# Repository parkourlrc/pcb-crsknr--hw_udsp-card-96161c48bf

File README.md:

# uDSP-Card: XCORE.AI Development Board for Portable Applications

This repository contains the hardware design files, pinout, and architectural documentation for the uDSP-Card, a small development board built around the XMOS XU316. Originally designed for a wearable ultrasonic sensing system, the board offers rich I/O and high-performance DSP capabilities at low power, making it ideal for audio, sensing, and real-time embedded tasks.

This repository accompanies the blog post "[uDSP-Card: XCORE.AI Development Board for Portable Applications](https://crsknr.github.io/blog/blog/udsp-card)".

## Repository Contents

- `kicad_udsp-card/`: KiCAD project folder containing schematics and PCB layout  
- `uDSP-Card_HAD.pdf`: Hardware architecture design (HAD) documentation  
- `uDSP-Card_XMOS-XU316-pinout.xlsx`: Processor pin assignments

## Board Overview

The uDSP-Card is powered by the XMOS XU316, a dual-core, 800 MHz processor with 16 logical cores and a vector unit. The board is derived from the XMOS reference design and development board XK-EVK-XU316[^1].

### Key Specifications

- **Dimensions:** 60 mm × 30 mm (6-layer PCB)
- **Processor:** XMOS XU316-1024 (dual-core, 800 MHz, 16 threads)
- **RAM:** 128 Mb LPDDR1
- **Flash:** 32 Mb QSPI
- **microSD** card slot
- **USB Interface:** Device (power + audio/data)
- **Line Output:** Stereo via ESS ES9033 DAC
- **Expansion Header:** 44-pin interconnect
  - I²S (8ch)
  - I²C / SPI
  - PDM (8ch)
  - Power input
- **Onboard Sensors:**
  - BMI323 IMU (accelerometer + gyro)
  - BME280 EMU (humidity, pressure, temperature)

## Board support

[`lib_udsp-card_board_support`](https://github.com/crsknr/lib_udsp-card_board_support): XMOS board support package and configuration files for firmware development.

## License

This project is licensed under the [GNU General Public License v3.0](https://www.gnu.org/licenses/gpl-3.0.en.html).

[^1]: **XMOS**, *"xcore.ai Explorer v2 BoardManual"*, Manual XM014531A, (2024)

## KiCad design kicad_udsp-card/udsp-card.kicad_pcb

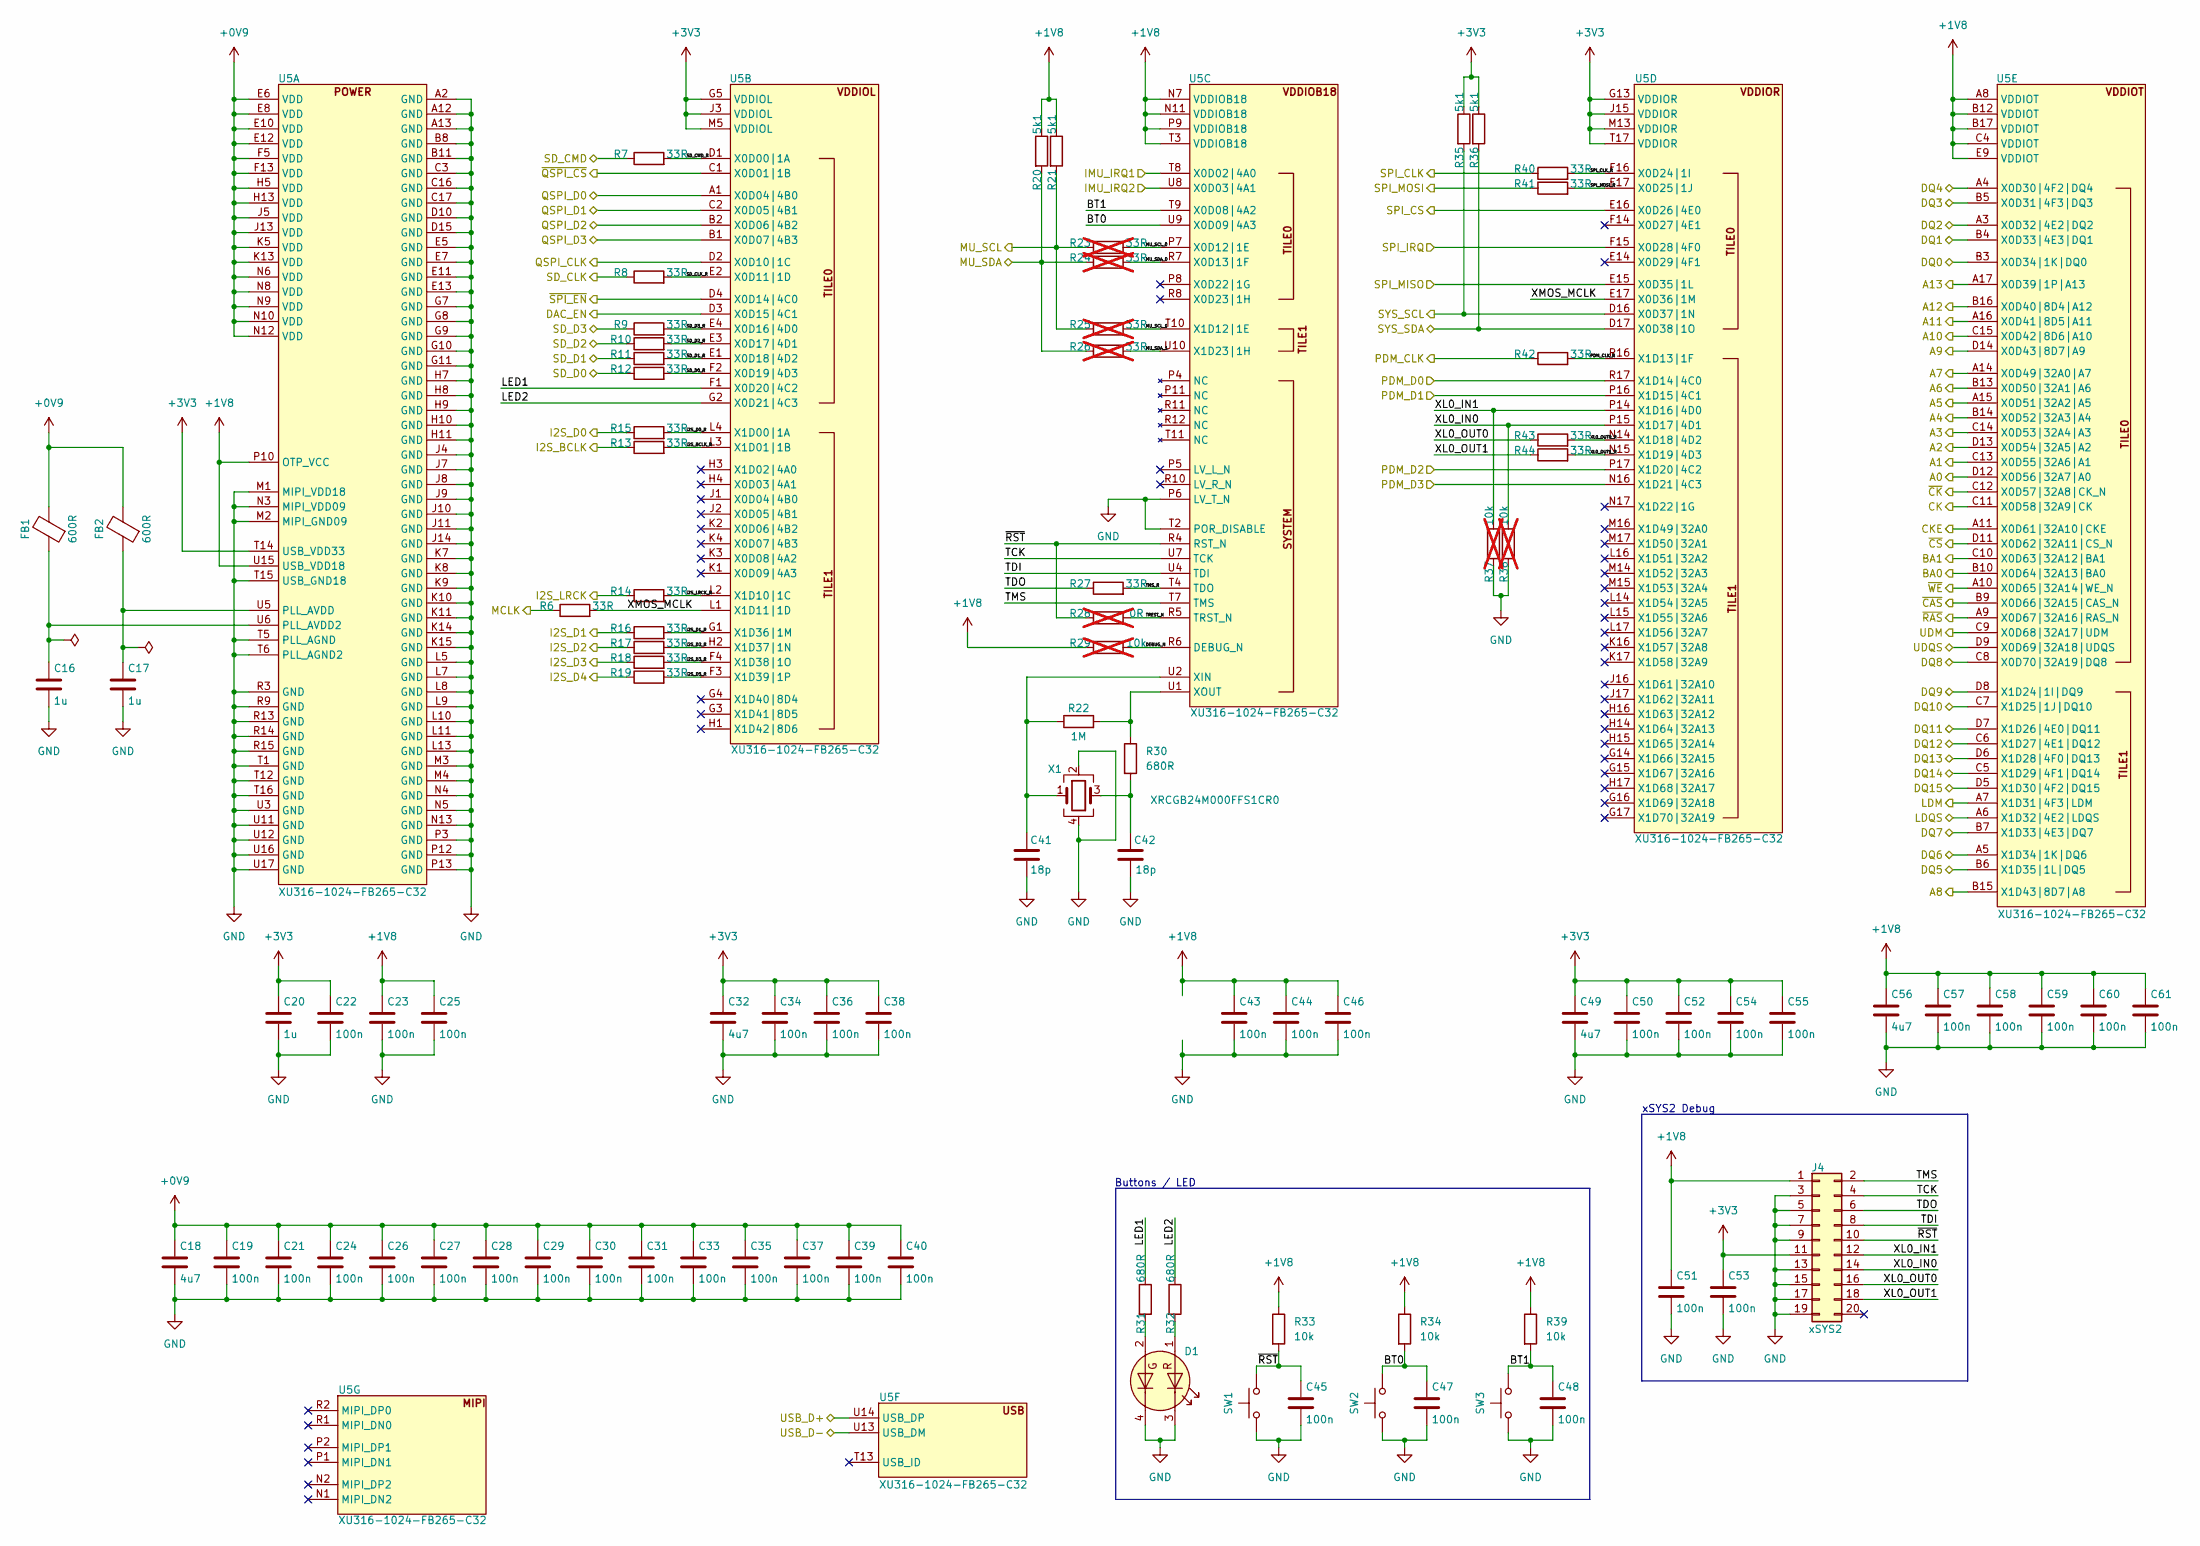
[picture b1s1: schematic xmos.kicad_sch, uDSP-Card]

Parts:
C16, C17, C20: 1u; C_0402_1005Metric; Part Number CC0402KRX5R7BB105
C18, C32, C49, C56: 4u7; C_0603_1608Metric; Part Number CC0603KRX5R7BB475
C19, C21, C22, C23, C24, C25, C26, C27, C28, C29, C30, C31, C33, C34, C35, C36, C37, C38, C39, C40, C43, C44, C45, C46, C47, C48, C50, C51, C52, C53, C54, C55, C57, C58, C59, C60, C61: 100n; C_0402_1005Metric; Part Number CC0402KRX5R9BB104
C41, C42: 18p; C_0402_1005Metric; Part Number CC0402JRNPO9BN180
D1: LTST-C195KGJRKT; LTST-C195KGJRKT-NPC_LTO; Part Number LTST-C195KGJRKT
FB1, FB2: 600R; L_0402_1005Metric; Part Number BLM15PX601SH1D
J4: xSYS2; SAMTEC_FTSH-110-01-F-DV-TR; Part Number FTSH-110-01-F-DV-K
R6, R7, R8, R9, R10, R11, R12, R13, R14, R15, R16, R17, R18, R19, R27, R40, R41, R42, R43, R44: 33R; R_0402_1005Metric; Part Number RC0402FR-0733RL
R20, R21, R35, R36: 5k1; R_0402_1005Metric; Part Number RC0402FR-075K1L
R22: 1M; R_0402_1005Metric; Part Number RC0402FR-071ML
R23, R24, R25, R26: 33R; R_0402_1005Metric; Part Number RC0402FR-7D33RL; not fitted
R28: 0R; R_0402_1005Metric; not fitted
R29, R37, R38: 10k; R_0402_1005Metric; not fitted
R30, R31, R32: 680R; R_0402_1005Metric; Part Number RC0402FR-07680RL
R33, R34, R39: 10k; R_0402_1005Metric; Part Number RC0402FR-0710KL
SW1, SW2, SW3: EVQ-P2F02K; EVQP2K_PAN; Part Number EVQ-P2F02K
U5: XU316-1024-FB265-C32; TFBGA-265_14x14mm_Layout17x17_P0.8mm; Part Number XU316-1024-FB265-C32
X1: XRCGB24M000FFS1CR0; XRCGB24_MUR; Part Number XRCGB24M000FFS1CR0

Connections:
+0V9: C18.1, C19.1, C21.1, C24.1, C26.1, C27.1, C28.1, C29.1, C30.1, C31.1, C33.1, C35.1, C37.1, C39.1, C40.1, FB1.2, FB2.2, U5.E6 (VDD), U5.E8 (VDD), U5.E10 (VDD), U5.E12 (VDD), U5.F5 (VDD), U5.F13 (VDD), U5.H5 (VDD), U5.H13 (VDD), U5.J5 (VDD), U5.J13 (VDD), U5.K5 (VDD), U5.K13 (VDD), U5.N6 (VDD), U5.N8 (VDD), U5.N9 (VDD), U5.N10 (VDD), U5.N12 (VDD); also elsewhere on the board
+1V8: C23.1, C25.1, C43.1, C44.1, C46.1, C51.1, C56.1, C57.1, C58.1, C59.1, C60.1, C61.1, J4.1, R20.1, R21.1, R29.1, R33.1, R34.1, R39.1, U5.A8 (VDDIOT), U5.B12 (VDDIOT), U5.B17 (VDDIOT), U5.C4 (VDDIOT), U5.E9 (VDDIOT), U5.N7 (VDDIOB18), U5.N11 (VDDIOB18), U5.P9 (VDDIOB18), U5.P10 (OTP_VCC), U5.T3 (VDDIOB18), U5.U15 (USB_VDD18); also elsewhere on the board
+3V3: C20.1, C22.1, C32.1, C34.1, C36.1, C38.1, C49.1, C50.1, C52.1, C53.1, C54.1, C55.1, J4.11, R35.1, R36.1, U5.G5 (VDDIOL), U5.G13 (VDDIOR), U5.J3 (VDDIOL), U5.J15 (VDDIOR), U5.M5 (VDDIOL), U5.M13 (VDDIOR), U5.T14 (USB_VDD33), U5.T17 (VDDIOR); also elsewhere on the board
/DAC_EN: U5.D3 (X0D15|4C1); also elsewhere on the board
/I2S.BCLK: R13.1; also elsewhere on the board
/I2S.D0: R15.1; also elsewhere on the board
/I2S.D1: R16.1; also elsewhere on the board
/I2S.D2: R17.1; also elsewhere on the board
/I2S.D3: R18.1; also elsewhere on the board
/I2S.D4: R19.1; also elsewhere on the board
/I2S.LRCK: R14.1; also elsewhere on the board
/I2S.MCLK: R6.1; also elsewhere on the board
/IMU_IRQ1: U5.T8 (X0D02|4A0); also elsewhere on the board
/IMU_IRQ2: U5.U8 (X0D03|4A1); also elsewhere on the board
/LPDDR_ADDR.A0: U5.D12 (X0D56|32A7|A0); also elsewhere on the board
/LPDDR_ADDR.A1: U5.C13 (X0D55|32A6|A1); also elsewhere on the board
/LPDDR_ADDR.A2: U5.D13 (X0D54|32A5|A2); also elsewhere on the board
/LPDDR_ADDR.A3: U5.C14 (X0D53|32A4|A3); also elsewhere on the board
/LPDDR_ADDR.A4: U5.B14 (X0D52|32A3|A4); also elsewhere on the board
/LPDDR_ADDR.A5: U5.A15 (X0D51|32A2|A5); also elsewhere on the board
/LPDDR_ADDR.A6: U5.B13 (X0D50|32A1|A6); also elsewhere on the board
/LPDDR_ADDR.A7: U5.A14 (X0D49|32A0|A7); also elsewhere on the board
/LPDDR_ADDR.A8: U5.B15 (X1D43|8D7|A8); also elsewhere on the board
/LPDDR_ADDR.A9: U5.D14 (X0D43|8D7|A9); also elsewhere on the board
/LPDDR_ADDR.A10: U5.C15 (X0D42|8D6|A10); also elsewhere on the board
/LPDDR_ADDR.A11: U5.A16 (X0D41|8D5|A11); also elsewhere on the board
/LPDDR_ADDR.A12: U5.B16 (X0D40|8D4|A12); also elsewhere on the board
/LPDDR_ADDR.A13: U5.A17 (X0D39|1P|A13); also elsewhere on the board
/LPDDR_CTRL.BA0: U5.B10 (X0D64|32A13|BA0); also elsewhere on the board
/LPDDR_CTRL.BA1: U5.C10 (X0D63|32A12|BA1); also elsewhere on the board
/LPDDR_CTRL.CK+: U5.C11 (X0D58|32A9|CK); also elsewhere on the board
/LPDDR_CTRL.CK-: U5.C12 (X0D57|32A8|CK_N); also elsewhere on the board
/LPDDR_CTRL.CKE: U5.A11 (X0D61|32A10|CKE); also elsewhere on the board
/LPDDR_CTRL.~CAS: U5.B9 (X0D66|32A15|CAS_N); also elsewhere on the board
/LPDDR_CTRL.~CS: U5.D11 (X0D62|32A11|CS_N); also elsewhere on the board
/LPDDR_CTRL.~RAS: U5.A9 (X0D67|32A16|RAS_N); also elsewhere on the board
/LPDDR_CTRL.~WE: U5.A10 (X0D65|32A14|WE_N); also elsewhere on the board
/LPDDR_LD.DQ0: U5.B3 (X0D34|1K|DQ0); also elsewhere on the board
/LPDDR_LD.DQ1: U5.B4 (X0D33|4E3|DQ1); also elsewhere on the board
/LPDDR_LD.DQ2: U5.A3 (X0D32|4E2|DQ2); also elsewhere on the board
/LPDDR_LD.DQ3: U5.B5 (X0D31|4F3|DQ3); also elsewhere on the board
/LPDDR_LD.DQ4: U5.A4 (X0D30|4F2|DQ4); also elsewhere on the board
/LPDDR_LD.DQ5: U5.B6 (X1D35|1L|DQ5); also elsewhere on the board
/LPDDR_LD.DQ6: U5.A5 (X1D34|1K|DQ6); also elsewhere on the board
/LPDDR_LD.DQ7: U5.B7 (X1D33|4E3|DQ7); also elsewhere on the board
/LPDDR_LD.LDM: U5.A7 (X1D31|4F3|LDM); also elsewhere on the board
/LPDDR_LD.LDQS: U5.A6 (X1D32|4E2|LDQS); also elsewhere on the board
/LPDDR_UD.DQ8: U5.C8 (X0D70|32A19|DQ8); also elsewhere on the board
/LPDDR_UD.DQ9: U5.D8 (X1D24|1I|DQ9); also elsewhere on the board
/LPDDR_UD.DQ10: U5.C7 (X1D25|1J|DQ10); also elsewhere on the board
/LPDDR_UD.DQ11: U5.D7 (X1D26|4E0|DQ11); also elsewhere on the board
/LPDDR_UD.DQ12: U5.C6 (X1D27|4E1|DQ12); also elsewhere on the board
/LPDDR_UD.DQ13: U5.D6 (X1D28|4F0|DQ13); also elsewhere on the board
/LPDDR_UD.DQ14: U5.C5 (X1D29|4F1|DQ14); also elsewhere on the board
/LPDDR_UD.DQ15: U5.D5 (X1D30|4F2|DQ15); also elsewhere on the board
/LPDDR_UD.UDM: U5.C9 (X0D68|32A17|UDM); also elsewhere on the board
/LPDDR_UD.UDQS: U5.D9 (X0D69|32A18|UDQS); also elsewhere on the board
/MIC.CLK: R42.1; also elsewhere on the board
/MIC.D0: U5.R17 (X1D14|4C0); also elsewhere on the board
/MIC.D1: U5.P16 (X1D15|4C1); also elsewhere on the board
/MIC.D2: U5.P17 (X1D20|4C2); also elsewhere on the board
/MIC.D3: U5.N16 (X1D21|4C3); also elsewhere on the board
/MU.SCL: R21.2, R23.1, R25.1; also elsewhere on the board
/MU.SDA: R20.2, R24.1, R26.1; also elsewhere on the board
/QSPI.CLK: U5.D2 (X0D10|1C); also elsewhere on the board
/QSPI.D0: U5.A1 (X0D04|4B0); also elsewhere on the board
/QSPI.D1: U5.C2 (X0D05|4B1); also elsewhere on the board
/QSPI.D2: U5.B2 (X0D06|4B2); also elsewhere on the board
/QSPI.D3: U5.B1 (X0D07|4B3); also elsewhere on the board
/QSPI.~CS: U5.C1 (X0D01|1B); also elsewhere on the board
/SD.CLK: R8.1; also elsewhere on the board
/SD.CMD: R7.1; also elsewhere on the board
/SD.D0: R12.1; also elsewhere on the board
/SD.D1: R11.1; also elsewhere on the board
/SD.D2: R10.1; also elsewhere on the board
/SD.D3: R9.1; also elsewhere on the board
/SPI.CLK: R40.1; also elsewhere on the board
/SPI.CS: U5.E16 (X0D26|4E0); also elsewhere on the board
/SPI.MISO: U5.E15 (X0D35|1L); also elsewhere on the board
/SPI.MOSI: R41.1; also elsewhere on the board
/SPI_IRQ: U5.F15 (X0D28|4F0); also elsewhere on the board
/SYS.SCL: R35.2, U5.D16 (X0D37|1N); also elsewhere on the board
/SYS.SDA: R36.2, U5.D17 (X0D38|1O); also elsewhere on the board
/USB.D+: U5.U14 (USB_DP); also elsewhere on the board
/USB.D-: U5.U13 (USB_DM); also elsewhere on the board
/XMOS/BT0: C47.1, R34.2, SW2.2, U5.U9 (X0D09|4A3)
/XMOS/BT1: C48.1, R39.2, SW3.2, U5.T9 (X0D08|4A2)
/XMOS/DEBUG_N: R29.2, U5.R6 (DEBUG_N)
/XMOS/I2S_BCLK_R: R13.2, U5.L3 (X1D01|1B)
/XMOS/I2S_D0_R: R15.2, U5.L4 (X1D00|1A)
/XMOS/I2S_D1_R: R16.2, U5.G1 (X1D36|1M)
/XMOS/I2S_D2_R: R17.2, U5.H2 (X1D37|1N)
/XMOS/I2S_D3_R: R18.2, U5.F4 (X1D38|1O)
/XMOS/I2S_D5_R: R19.2, U5.F3 (X1D39|1P)
/XMOS/I2S_LRCK_R: R14.2, U5.L2 (X1D10|1C)
/XMOS/LED1: R31.1, U5.F1 (X0D20|4C2)
/XMOS/LED2: R32.1, U5.G2 (X0D21|4C3)
/XMOS/MU_SCL_0: R23.2, U5.P7 (X0D12|1E)
/XMOS/MU_SCL_1: R25.2, U5.T10 (X1D12|1E)
/XMOS/MU_SDA_0: R24.2, U5.R7 (X0D13|1F)
/XMOS/MU_SDA_1: R26.2, U5.U10 (X1D23|1H)
/XMOS/PDM_CLK_R: R42.2, U5.R16 (X1D13|1F)
/XMOS/SD_CLK_R: R8.2, U5.E2 (X0D11|1D)
/XMOS/SD_CMD_R: R7.2, U5.D1 (X0D00|1A)
/XMOS/SD_D0_R: R12.2, U5.F2 (X0D19|4D3)
/XMOS/SD_D1_R: R11.2, U5.E1 (X0D18|4D2)
/XMOS/SD_D2_R: R10.2, U5.E3 (X0D17|4D1)
/XMOS/SD_D3_R: R9.2, U5.E4 (X0D16|4D0)
/XMOS/SPI_CLK_R: R40.2, U5.F16 (X0D24|1I)
/XMOS/SPI_MOSI_R: R41.2, U5.F17 (X0D25|1J)
/XMOS/TCK: J4.4, U5.U7 (TCK)
/XMOS/TDI: J4.8, U5.U4 (TDI)
/XMOS/TDO: J4.6, R27.1
/XMOS/TMS: J4.2, U5.T7 (TMS)
/XMOS/TMS_R: R27.2, U5.T4 (TDO)
/XMOS/TREST_N: R28.2, U5.R5 (TRST_N)
/XMOS/XL0_IN0: J4.14, R38.2, U5.P15 (X1D17|4D1)
/XMOS/XL0_IN1: J4.12, R37.2, U5.P14 (X1D16|4D0)
/XMOS/XL0_OUT0: J4.16, R43.1
/XMOS/XL0_OUT0_R: R43.2, U5.N14 (X1D18|4D2)
/XMOS/XL0_OUT1: J4.18, R44.1
/XMOS/XL0_OUT1_R: R44.2, U5.N15 (X1D19|4D3)
/XMOS/XMOS_MCLK: R6.2, U5.E17 (X0D36|1M), U5.L1 (X1D11|1D)
/XMOS/~RST: C45.1, J4.10, R28.1, R33.2, SW1.2, U5.R4 (RST_N)
/~SPI_EN: U5.D4 (X0D14|4C0); also elsewhere on the board
GND: C16.2, C17.2, C18.2, C19.2, C20.2, C21.2, C22.2, C23.2, C24.2, C25.2, C26.2, C27.2, C28.2, C29.2, C30.2, C31.2, C32.2, C33.2, C34.2, C35.2, C36.2, C37.2, C38.2, C39.2, C40.2, C41.2, C42.2, C43.2, C44.2, C45.2, C46.2, C47.2, C48.2, C49.2, C50.2, C51.2, C52.2, C53.2, C54.2, C55.2, C56.2, C57.2, C58.2, C59.2, C60.2, C61.2, D1.3 (K1), D1.4 (K2), J4.3, J4.5, J4.7, J4.9, J4.13, J4.15, J4.17, J4.19, R37.1, R38.1, SW1.1, SW2.1, SW3.1, U5.A2 (GND), U5.A12 (GND), U5.A13 (GND), U5.B8 (GND), U5.B11 (GND), U5.C3 (GND), U5.C16 (GND), U5.C17 (GND), U5.D10 (GND), U5.D15 (GND), U5.E5 (GND), U5.E7 (GND), U5.E11 (GND), U5.E13 (GND), U5.G7 (GND), U5.G8 (GND), U5.G9 (GND), U5.G10 (GND), U5.G11 (GND), U5.H7 (GND), U5.H8 (GND), U5.H9 (GND), U5.H10 (GND), U5.H11 (GND), U5.J4 (GND), U5.J7 (GND), U5.J8 (GND), U5.J9 (GND), U5.J10 (GND), U5.J11 (GND), U5.J14 (GND), U5.K7 (GND), U5.K8 (GND), U5.K9 (GND), U5.K10 (GND), U5.K11 (GND), U5.K14 (GND), U5.K15 (GND), U5.L5 (GND), U5.L7 (GND), U5.L8 (GND), U5.L9 (GND), U5.L10 (GND), U5.L11 (GND), U5.L13 (GND), U5.M1 (MIPI_VDD18), U5.M2 (MIPI_GND09), U5.M3 (GND), U5.M4 (GND), U5.N3 (MIPI_VDD09), U5.N4 (GND), U5.N5 (GND), U5.N13 (GND), U5.P3 (GND), U5.P6 (LV_T_N), U5.P12 (GND), U5.P13 (GND), U5.R3 (GND), U5.R9 (GND), U5.R13 (GND), U5.R14 (GND), U5.R15 (GND), U5.T1 (GND), U5.T2 (POR_DISABLE), U5.T5 (PLL_AGND), U5.T6 (PLL_AGND2), U5.T12 (GND), U5.T15 (USB_GND18), U5.T16 (GND), U5.U3 (GND), U5.U11 (GND), U5.U12 (GND), U5.U16 (GND), U5.U17 (GND), X1.2, X1.4; also elsewhere on the board
unnamed: C42.1, R30.2, X1.3
unnamed: D1.1 (A1), R32.2
unnamed: D1.2 (A2), R31.2
unnamed: C16.1, FB1.1, U5.U6 (PLL_AVDD2)
unnamed: C17.1, FB2.1, U5.U5 (PLL_AVDD)
unnamed: C41.1, R22.1, U5.U2 (XIN), X1.1
unnamed: R22.2, R30.1, U5.U1 (XOUT)

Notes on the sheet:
Buttons / LED
xSYS2 Debug

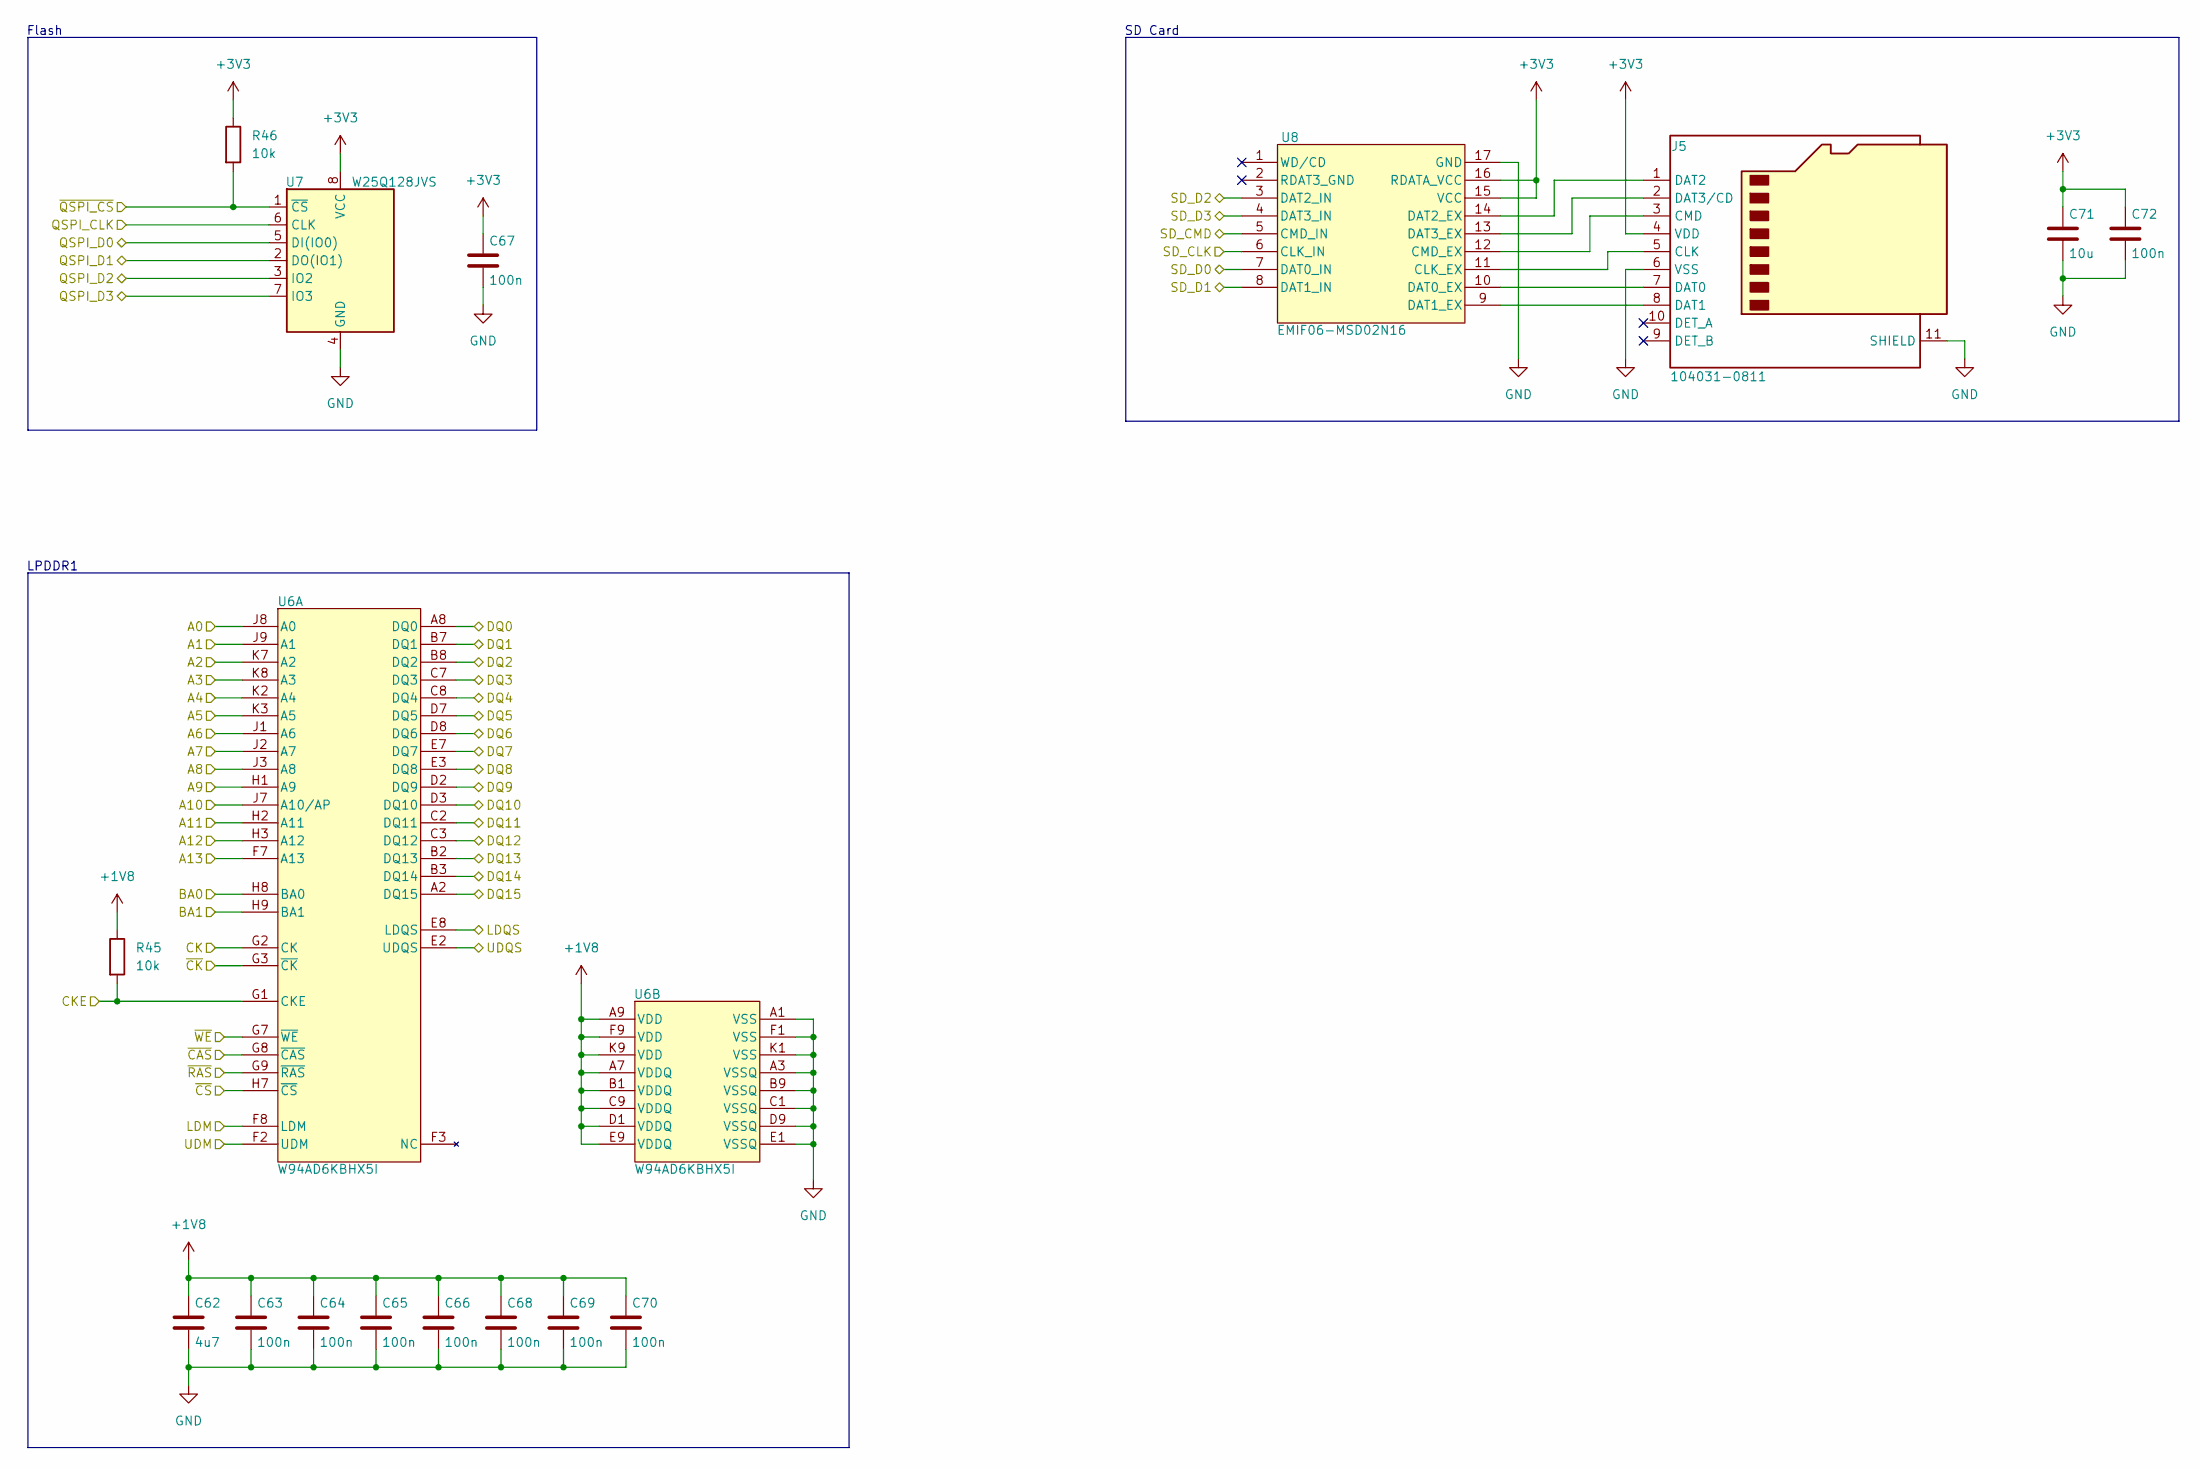
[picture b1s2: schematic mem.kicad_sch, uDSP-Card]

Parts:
C62: 4u7; C_0603_1608Metric; Part Number CC0603KRX5R7BB475
C63, C64, C65, C66, C67, C68, C69, C70, C72: 100n; C_0402_1005Metric; Part Number CC0402KRX5R9BB104
C71: 10u; C_0603_1608Metric; Part Number CC0603MRX5R7BB106
J5: 104031-0811; microSD_HC_Molex_104031-0811; Part Number 104031-0811
R45, R46: 10k; R_0402_1005Metric; Part Number RC0402FR-0710KL
U6: W94AD6KBHX5I; WIN_VFBGA-60_WIN; Part Number W94AD6KBHX5I
U7: W25Q128JVS; SOIC-8_5.23x5.23mm_P1.27mm; Part Number W25Q128JVSIM
U8: EMIF06-MSD02N16; MICROQFN16_1P25X3P55X0P4_STM; Part Number EMIF06-MSD02N16

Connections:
+1V8: C62.1, C63.1, C64.1, C65.1, C66.1, C68.1, C69.1, C70.1, R45.1, U6.A7 (VDDQ), U6.A9 (VDD), U6.B1 (VDDQ), U6.C9 (VDDQ), U6.D1 (VDDQ), U6.E9 (VDDQ), U6.F9 (VDD), U6.K9 (VDD); also elsewhere on the board
+3V3: C67.1, C71.1, C72.1, J5.4 (VDD), R46.1, U7.8 (VCC), U8.15 (VCC), U8.16 (RDATA_VCC); also elsewhere on the board
/LPDDR_ADDR.A0: U6.J8 (A0); also elsewhere on the board
/LPDDR_ADDR.A1: U6.J9 (A1); also elsewhere on the board
/LPDDR_ADDR.A2: U6.K7 (A2); also elsewhere on the board
/LPDDR_ADDR.A3: U6.K8 (A3); also elsewhere on the board
/LPDDR_ADDR.A4: U6.K2 (A4); also elsewhere on the board
/LPDDR_ADDR.A5: U6.K3 (A5); also elsewhere on the board
/LPDDR_ADDR.A6: U6.J1 (A6); also elsewhere on the board
/LPDDR_ADDR.A7: U6.J2 (A7); also elsewhere on the board
/LPDDR_ADDR.A8: U6.J3 (A8); also elsewhere on the board
/LPDDR_ADDR.A9: U6.H1 (A9); also elsewhere on the board
/LPDDR_ADDR.A10: U6.J7 (A10/AP); also elsewhere on the board
/LPDDR_ADDR.A11: U6.H2 (A11); also elsewhere on the board
/LPDDR_ADDR.A12: U6.H3 (A12); also elsewhere on the board
/LPDDR_ADDR.A13: U6.F7 (A13); also elsewhere on the board
/LPDDR_CTRL.BA0: U6.H8 (BA0); also elsewhere on the board
/LPDDR_CTRL.BA1: U6.H9 (BA1); also elsewhere on the board
/LPDDR_CTRL.CK+: U6.G2 (CK); also elsewhere on the board
/LPDDR_CTRL.CK-: U6.G3 (~CK); also elsewhere on the board
/LPDDR_CTRL.CKE: R45.2, U6.G1 (CKE); also elsewhere on the board
/LPDDR_CTRL.~CAS: U6.G8 (~CAS); also elsewhere on the board
/LPDDR_CTRL.~CS: U6.H7 (~CS); also elsewhere on the board
/LPDDR_CTRL.~RAS: U6.G9 (~RAS); also elsewhere on the board
/LPDDR_CTRL.~WE: U6.G7 (~WE); also elsewhere on the board
/LPDDR_LD.DQ0: U6.A8 (DQ0); also elsewhere on the board
/LPDDR_LD.DQ1: U6.B7 (DQ1); also elsewhere on the board
/LPDDR_LD.DQ2: U6.B8 (DQ2); also elsewhere on the board
/LPDDR_LD.DQ3: U6.C7 (DQ3); also elsewhere on the board
/LPDDR_LD.DQ4: U6.C8 (DQ4); also elsewhere on the board
/LPDDR_LD.DQ5: U6.D7 (DQ5); also elsewhere on the board
/LPDDR_LD.DQ6: U6.D8 (DQ6); also elsewhere on the board
/LPDDR_LD.DQ7: U6.E7 (DQ7); also elsewhere on the board
/LPDDR_LD.LDM: U6.F8 (LDM); also elsewhere on the board
/LPDDR_LD.LDQS: U6.E8 (LDQS); also elsewhere on the board
/LPDDR_UD.DQ8: U6.E3 (DQ8); also elsewhere on the board
/LPDDR_UD.DQ9: U6.D2 (DQ9); also elsewhere on the board
/LPDDR_UD.DQ10: U6.D3 (DQ10); also elsewhere on the board
/LPDDR_UD.DQ11: U6.C2 (DQ11); also elsewhere on the board
/LPDDR_UD.DQ12: U6.C3 (DQ12); also elsewhere on the board
/LPDDR_UD.DQ13: U6.B2 (DQ13); also elsewhere on the board
/LPDDR_UD.DQ14: U6.B3 (DQ14); also elsewhere on the board
/LPDDR_UD.DQ15: U6.A2 (DQ15); also elsewhere on the board
/LPDDR_UD.UDM: U6.F2 (UDM); also elsewhere on the board
/LPDDR_UD.UDQS: U6.E2 (UDQS); also elsewhere on the board
/QSPI.CLK: U7.6 (CLK); also elsewhere on the board
/QSPI.D0: U7.5 (DI(IO0)); also elsewhere on the board
/QSPI.D1: U7.2 (DO(IO1)); also elsewhere on the board
/QSPI.D2: U7.3 (IO2); also elsewhere on the board
/QSPI.D3: U7.7 (IO3); also elsewhere on the board
/QSPI.~CS: R46.2, U7.1 (~CS); also elsewhere on the board
/SD.CLK: U8.6 (CLK_IN); also elsewhere on the board
/SD.CMD: U8.5 (CMD_IN); also elsewhere on the board
/SD.D0: U8.7 (DAT0_IN); also elsewhere on the board
/SD.D1: U8.8 (DAT1_IN); also elsewhere on the board
/SD.D2: U8.3 (DAT2_IN); also elsewhere on the board
/SD.D3: U8.4 (DAT3_IN); also elsewhere on the board
GND: C62.2, C63.2, C64.2, C65.2, C66.2, C67.2, C68.2, C69.2, C70.2, C71.2, C72.2, J5.6 (VSS), J5.11 (SHIELD), U6.A1 (VSS), U6.A3 (VSSQ), U6.B9 (VSSQ), U6.C1 (VSSQ), U6.D9 (VSSQ), U6.E1 (VSSQ), U6.F1 (VSS), U6.K1 (VSS), U7.4 (GND), U8.17 (GND); also elsewhere on the board
unnamed: J5.5 (CLK), U8.11 (CLK_EX)
unnamed: J5.3 (CMD), U8.12 (CMD_EX)
unnamed: J5.7 (DAT0), U8.10 (DAT0_EX)
unnamed: J5.8 (DAT1), U8.9 (DAT1_EX)
unnamed: J5.1 (DAT2), U8.14 (DAT2_EX)
unnamed: J5.2 (DAT3/CD), U8.13 (DAT3_EX)

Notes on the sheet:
SD Card
Flash
LPDDR1

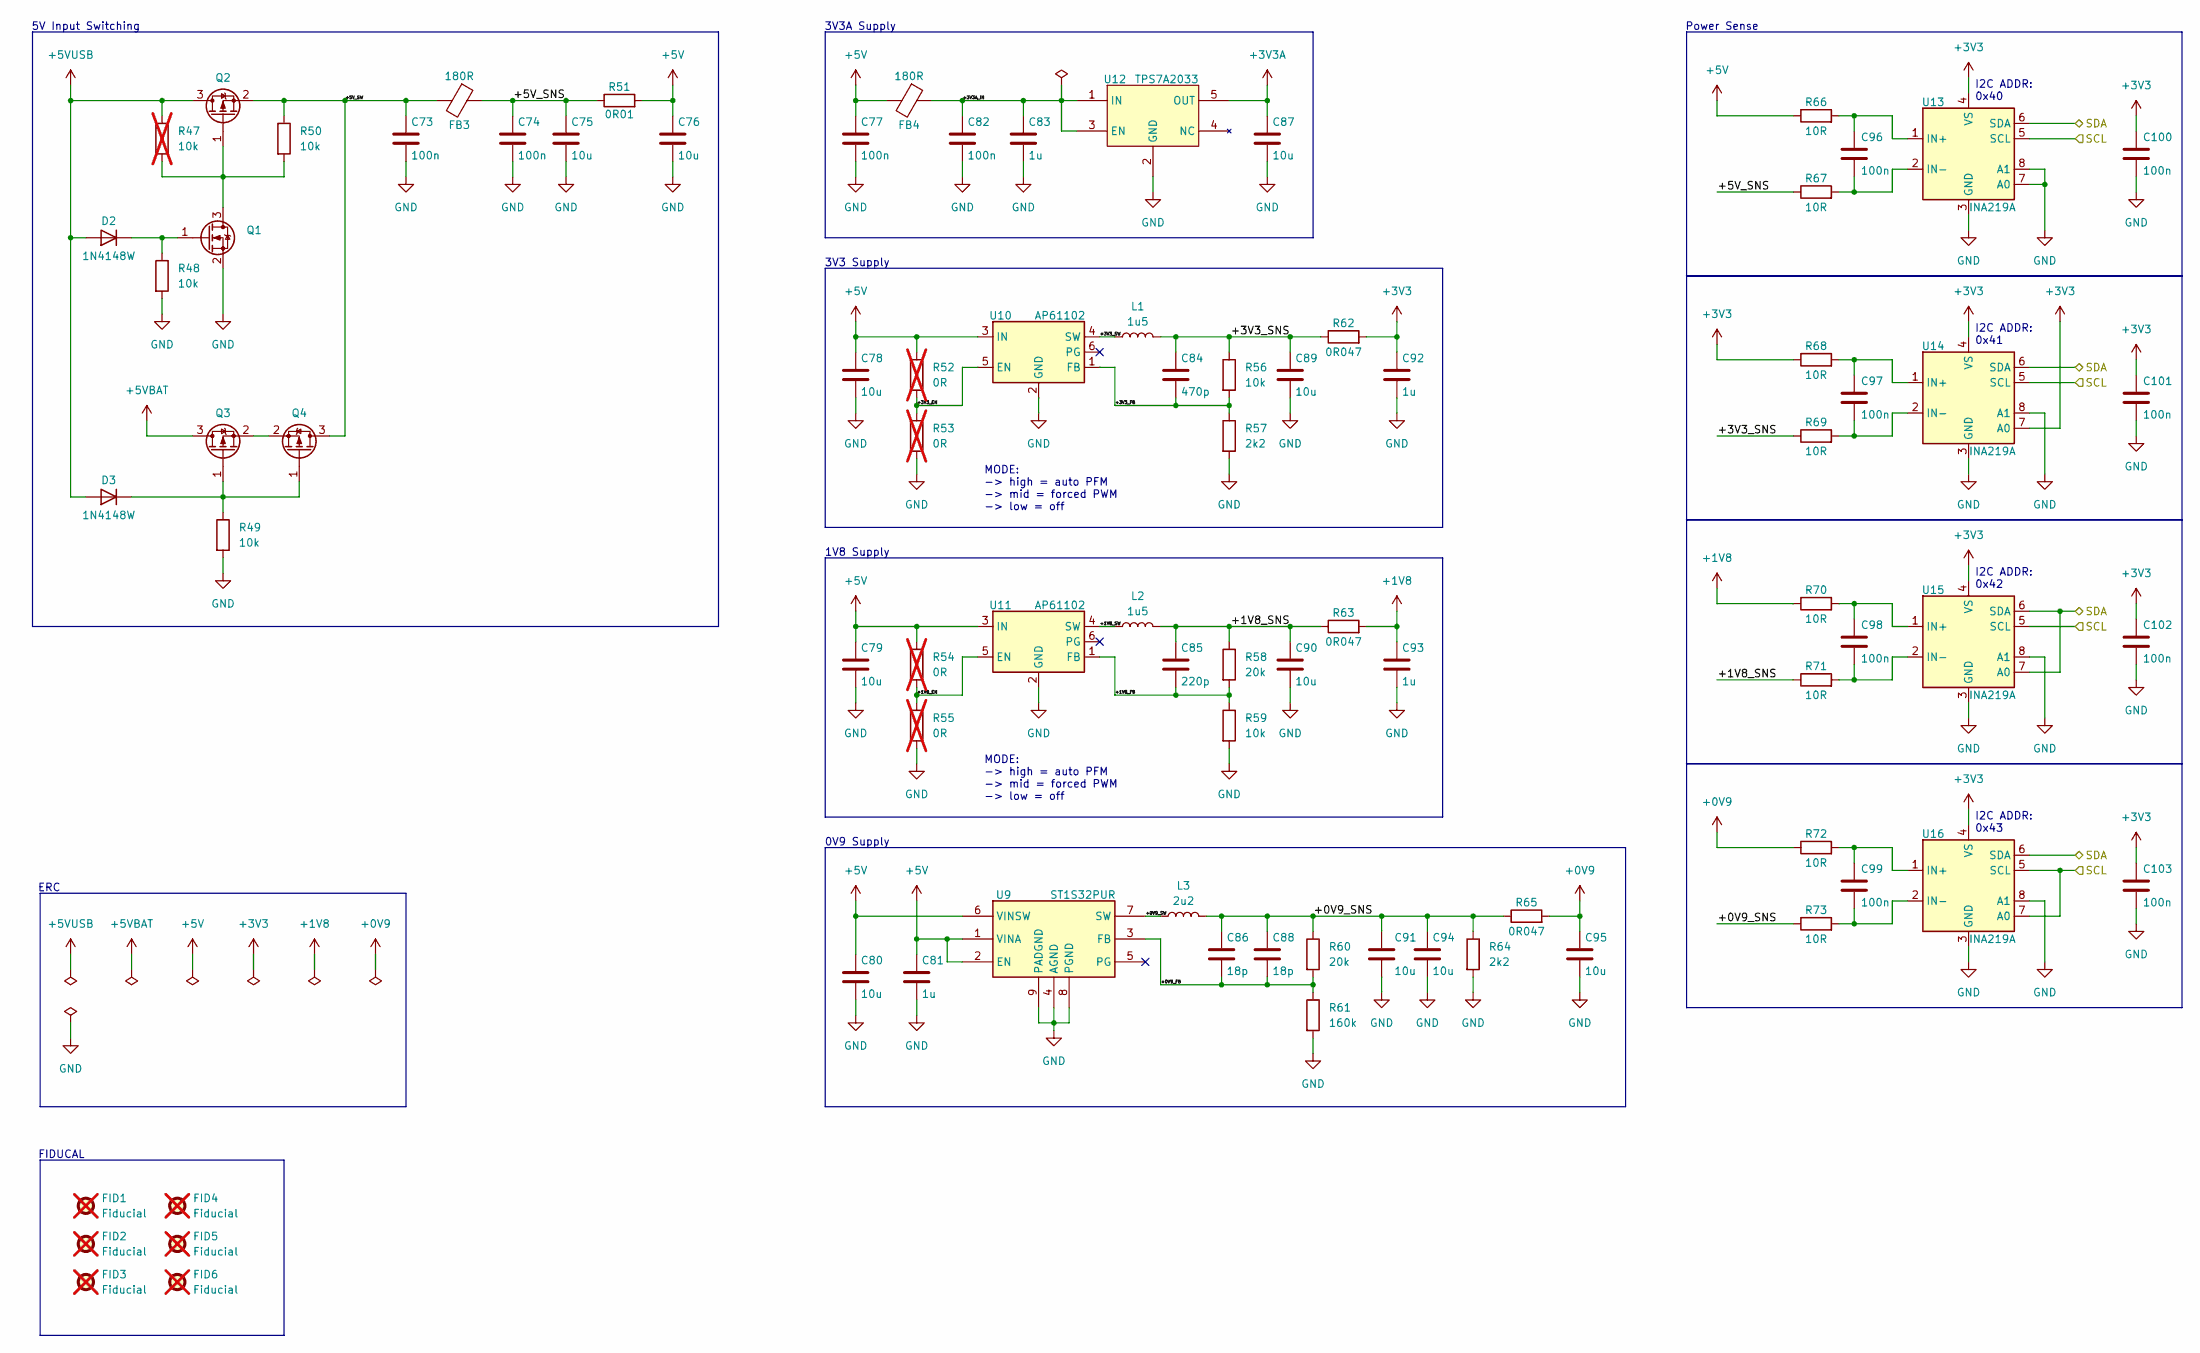
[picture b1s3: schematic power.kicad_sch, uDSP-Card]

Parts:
C73, C74, C77, C82, C96, C97, C98, C99, C100, C101, C102, C103: 100n; C_0402_1005Metric; Part Number CC0402KRX5R9BB104
C75, C76, C78, C79, C80, C87, C89, C90, C91, C94, C95: 10u; C_0603_1608Metric; Part Number CC0603MRX5R7BB106
C81, C83, C92, C93: 1u; C_0402_1005Metric; Part Number CC0402KRX5R7BB105
C84: 470p; C_0402_1005Metric; Part Number CC0402KRX7R7BB471
C85: 220p; C_0402_1005Metric; Part Number CC0402KRX7R7BB221
C86, C88: 18p; C_0402_1005Metric; Part Number CC0402JRNPO9BN180
D2, D3: 1N4148W; D_SOD-123F; Part Number 1N4148W-E3-08
FB3, FB4: 180R; L_0805_2012Metric; Part Number BLM21SP181SZ1D
FID1, FID2, FID3, FID4, FID5, FID6: Fiducial; Fiducial_0.5mm_Mask1.5mm; not fitted
L1, L2: 1u5; L_1008_2520Metric; Part Number MAMK2520H1R5M
L3: 2u2; L_Bourns-SRN6028; Part Number NR6028T2R2N
Q1: 2N7002; SOT-23; Part Number 2N7002A-7
Q2, Q3, Q4: RQ5C060BCTCL; SOT346; Part Number RQ5C060BCTCL
R47: 10k; R_0402_1005Metric; Part Number RC0402FR-0710KL; not fitted
R48, R49, R50, R56, R59: 10k; R_0402_1005Metric; Part Number RC0402FR-0710KL
R51: 0R01; R_0612_1632Metric; Part Number ERJ-D2DFR010V
R52, R53, R54, R55: 0R; R_0402_1005Metric; not fitted
R57, R64: 2k2; R_0402_1005Metric; Part Number RC0402FR-072K2L
R58, R60: 20k; R_0402_1005Metric; Part Number RC0402FR-0720KL
R61: 160k; R_0402_1005Metric; Part Number RC0402FR-07160KL
R62, R63, R65: 0R047; R_0612_1632Metric; Part Number ERJ-D2CFR047V
R66, R67, R68, R69, R70, R71, R72, R73: 10R; R_0402_1005Metric; Part Number RC0402FR-0710RL
U9: ST1S32PUR; SON_S32PUR_STM; Part Number ST1S32PUR
U10, U11: AP61102; SOT-563; Part Number AP61102Z6-7
U12: TPS7A2033; SOT-23-5; Part Number TPS7A2033PDBVR
U13, U14, U15, U16: INA219A; SOT-23-8; Part Number INA219AIDCNR

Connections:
+0V9: C95.1, R65.2, R72.1; also elsewhere on the board
+1V8: C93.1, R63.2, R70.1; also elsewhere on the board
+3V3: C92.1, C100.1, C101.1, C102.1, C103.1, R62.2, R68.1, U13.4 (VS), U14.4 (VS), U14.7 (A0), U15.4 (VS), U16.4 (VS); also elsewhere on the board
+3V3A: C87.1, U12.5 (OUT); also elsewhere on the board
+5V: C76.1, C77.1, C78.1, C79.1, C80.1, C81.1, FB4.2, R51.2, R52.1, R54.1, R66.1, U9.1 (VINA), U9.2 (EN), U9.6 (VINSW), U10.3 (IN), U11.3 (IN); also elsewhere on the board
+5VBAT: Q3.3 (D); also elsewhere on the board
+5VUSB: D2.2 (A), D3.2 (A), Q2.3 (D), R47.1; also elsewhere on the board
/Power/+0V9_FB: C86.2, C88.2, R60.2, R61.1, U9.3 (FB)
/Power/+0V9_SNS: C86.1, C88.1, C91.1, C94.1, L3.2, R60.1, R64.1, R65.1, R73.1
/Power/+0V9_SW: L3.1, U9.7 (SW)
/Power/+1V8_EN: R54.2, R55.1, U11.5 (EN)
/Power/+1V8_FB: C85.2, R58.2, R59.1, U11.1 (FB)
/Power/+1V8_SNS: C85.1, C90.1, L2.2, R58.1, R63.1, R71.1
/Power/+1V8_SW: L2.1, U11.4 (SW)
/Power/+3V3A_IN: C82.1, C83.1, FB4.1, U12.1 (IN), U12.3 (EN)
/Power/+3V3_EN: R52.2, R53.1, U10.5 (EN)
/Power/+3V3_FB: C84.2, R56.2, R57.1, U10.1 (FB)
/Power/+3V3_SNS: C84.1, C89.1, L1.2, R56.1, R62.1, R69.1
/Power/+3V3_SW: L1.1, U10.4 (SW)
/Power/+5V_SNS: C74.1, C75.1, FB3.1, R51.1, R67.1
/Power/+5V_SW: C73.1, FB3.2, Q2.2 (S), Q4.3 (D), R50.1
/SYS.SCL: U13.5 (SCL), U14.5 (SCL), U15.5 (SCL), U16.5 (SCL), U16.7 (A0); also elsewhere on the board
/SYS.SDA: U13.6 (SDA), U14.6 (SDA), U15.6 (SDA), U15.7 (A0), U16.6 (SDA); also elsewhere on the board
GND: C73.2, C74.2, C75.2, C76.2, C77.2, C78.2, C79.2, C80.2, C81.2, C82.2, C83.2, C87.2, C89.2, C90.2, C91.2, C92.2, C93.2, C94.2, C95.2, C100.2, C101.2, C102.2, C103.2, Q1.2 (S), R48.2, R49.2, R53.2, R55.2, R57.2, R59.2, R61.2, R64.2, U9.4 (AGND), U9.8 (PGND), U9.9 (PADGND), U10.2 (GND), U11.2 (GND), U12.2 (GND), U13.3 (GND), U13.7 (A0), U13.8 (A1), U14.3 (GND), U14.8 (A1), U15.3 (GND), U15.8 (A1), U16.3 (GND), U16.8 (A1); also elsewhere on the board
unnamed: D2.1 (K), Q1.1 (G), R48.1
unnamed: D3.1 (K), Q3.1 (G), Q4.1 (G), R49.1
unnamed: Q1.3 (D), Q2.1 (G), R47.2, R50.2
unnamed: Q3.2 (S), Q4.2 (S)
unnamed: C96.1, R66.2, U13.1 (IN+)
unnamed: C96.2, R67.2, U13.2 (IN-)
unnamed: C97.1, R68.2, U14.1 (IN+)
unnamed: C97.2, R69.2, U14.2 (IN-)
unnamed: C98.1, R70.2, U15.1 (IN+)
unnamed: C98.2, R71.2, U15.2 (IN-)
unnamed: C99.1, R72.2, U16.1 (IN+)
unnamed: C99.2, R73.2, U16.2 (IN-)

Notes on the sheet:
3V3A Supply
FIDUCAL
I2C ADDR: 0x41
MODE: -> high = auto PFM -> mid = forced PWM -> low = off
I2C ADDR: 0x40
Power Sense
I2C ADDR: 0x42
0V9 Supply
ERC
1V8 Supply
I2C ADDR: 0x43
5V Input Switching
3V3 Supply
